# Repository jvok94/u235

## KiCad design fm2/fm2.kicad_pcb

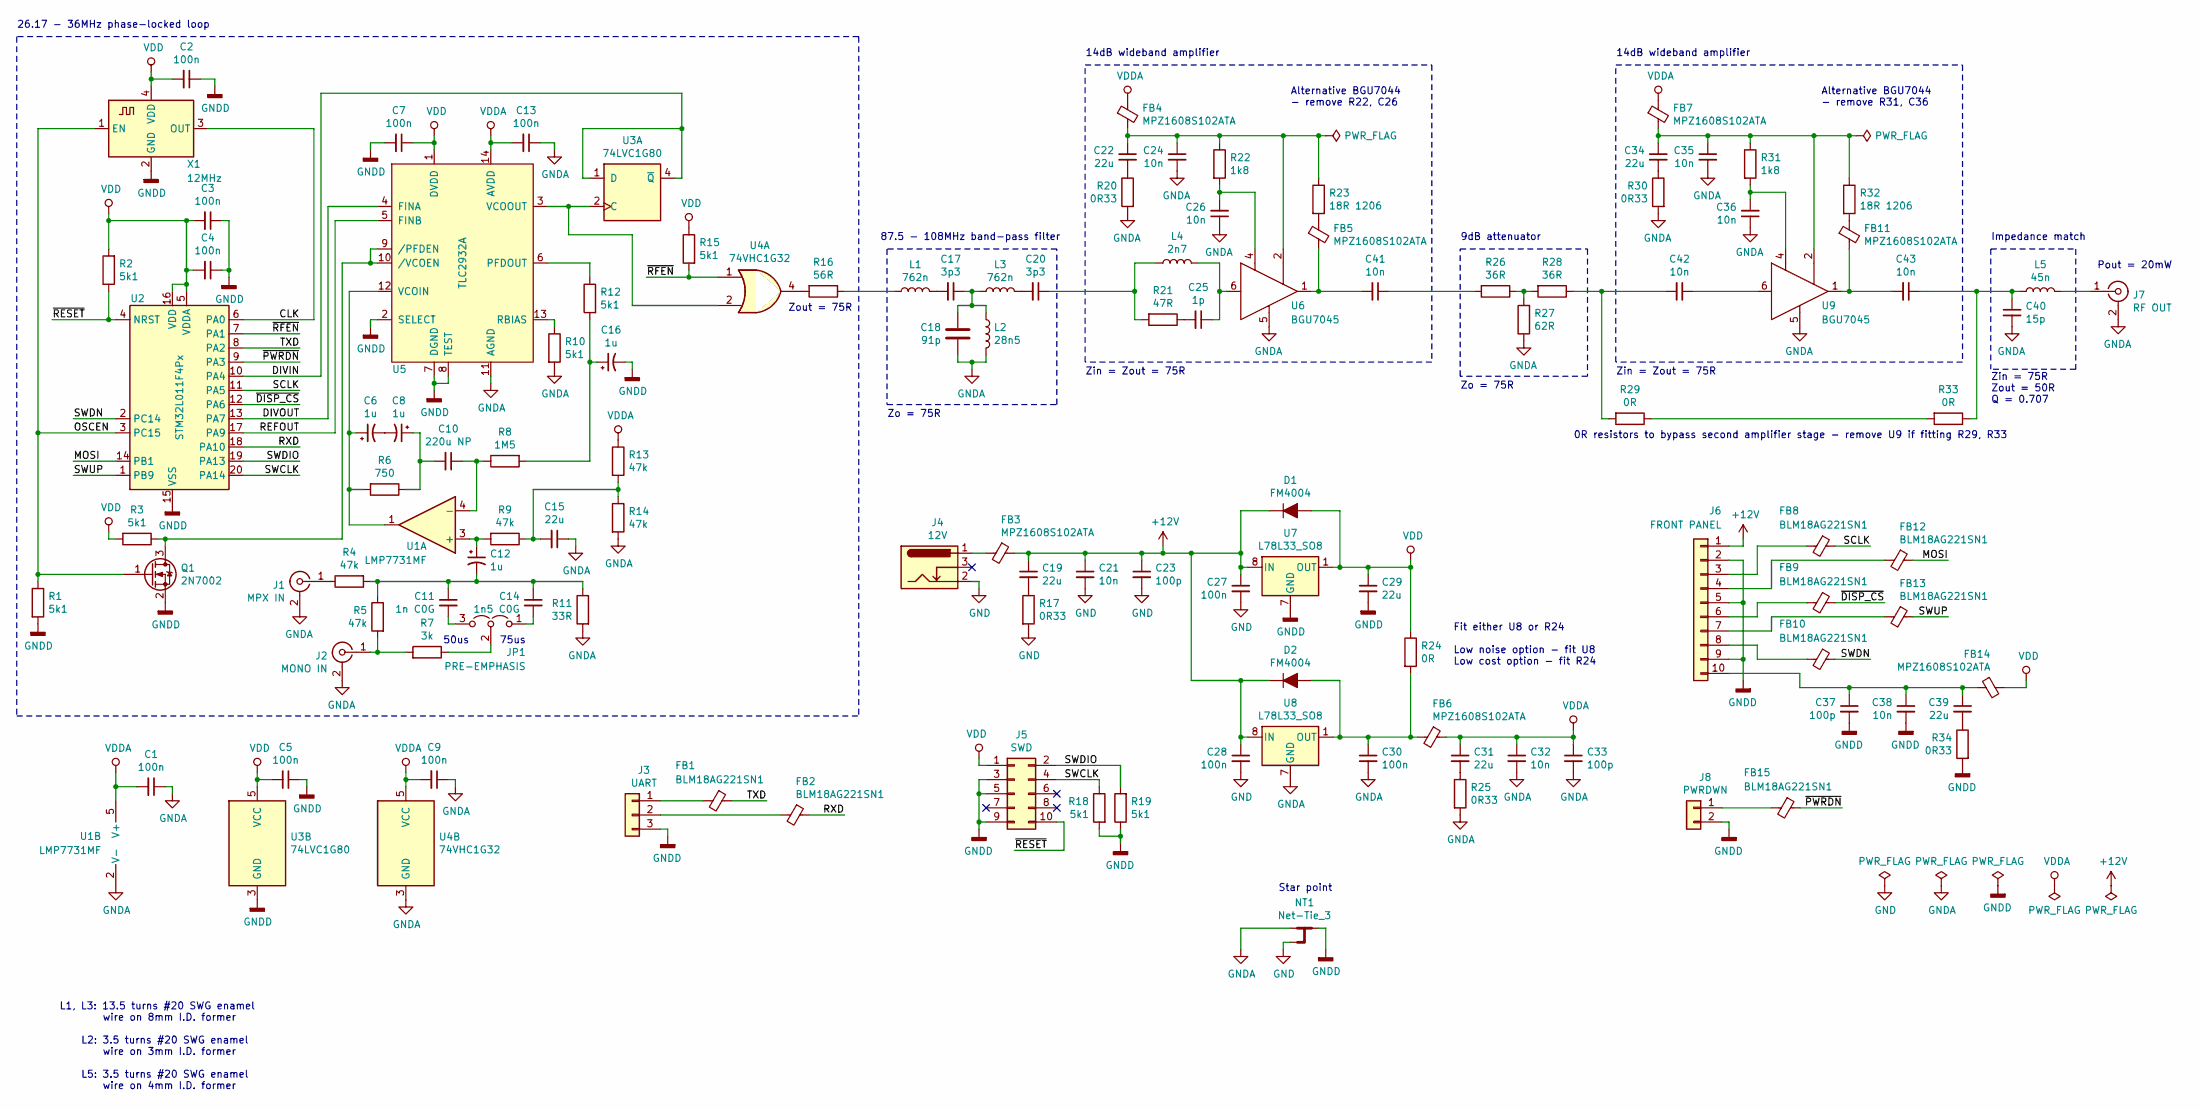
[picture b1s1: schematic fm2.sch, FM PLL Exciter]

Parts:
C1, C2, C3, C4, C5, C7, C9, C13, C27, C28, C30: 100n; C_0603_HandSoldering
C6, C8, C12, C16: 1u; CP_Radial_D5.0mm_P2.00mm
C10: 220u NP; CP_Radial_D8.0mm_P3.50mm
C11: 1n C0G; C_0603_HandSoldering
C14: 1n5 C0G; C_0603_HandSoldering
C15, C19, C22, C29, C31, C34, C39: 22u; C_1206_HandSoldering
C17, C20: 3p3; C_0603_HandSoldering
C18: 91p; C_0603_HandSoldering
C21, C24, C26, C32, C35, C36, C38, C41, C42, C43: 10n; C_0603_HandSoldering
C23, C33, C37: 100p; C_0603_HandSoldering
C25: 1p; C_0603_HandSoldering
C40: 15p; C_0603_HandSoldering
D1, D2: FM4004; D_SMA_Handsoldering
FB1, FB2, FB8, FB9, FB10, FB12, FB13, FB15: BLM18AG221SN1; R_0603_HandSoldering
FB3, FB4, FB5, FB6, FB7, FB11, FB14: MPZ1608S102ATA; R_0603_HandSoldering
J1: MPX IN; NYS354
J2: MONO IN; NYS354
J3: UART; Pin_Header_Straight_1x03_Pitch2.54mm
J4: 12V; BARREL_JACK
J5: SWD; Pin_Header_Straight_2x05_Pitch1.27mm
J6: FRONT PANEL; Pin_Header_Straight_1x10_Pitch2.54mm
J7: RF OUT; bnc-ci
J8: PWRDWN; Pin_Header_Straight_1x02_Pitch2.54mm
JP1: PRE-EMPHASIS; Pin_Header_Straight_1x03_Pitch2.54mm
L1, L3: 762n; Coil_D10mm_L14mm
L2: 28n5; Coil_D5mm_L4mm
L4: 2n7; R_0402_NoSilk
L5: 45n; Coil_D6mm_L4mm
NT1: Net-Tie_3; net_tie_3
Q1: 2N7002; SOT-23_Handsoldering
R1, R2, R3, R10, R12, R15, R18, R19: 5k1; R_0603_HandSoldering
R4, R5, R9, R13, R14: 47k; R_0603_HandSoldering
R6: 750; R_0603_HandSoldering
R7: 3k; R_0603_HandSoldering
R8: 1M5; R_0603_HandSoldering
R11: 33R; R_0603_HandSoldering
R16: 56R; R_0603_HandSoldering
R17, R20, R25, R30, R34: 0R33; R_0603_HandSoldering
R21: 47R; R_0603_HandSoldering
R22, R31: 1k8; R_0603_HandSoldering
R23, R32: 18R 1206; R_1206_HandSoldering
R24, R29, R33: 0R; R_0603_HandSoldering
R26, R28: 36R; R_0603_HandSoldering
R27: 62R; R_0603_HandSoldering
U1: LMP7731MF; SOT-23-5_HandSoldering
U2: STM32L011F4Px; TSSOP-20_4.4x6.5mm_P0.65mm
U3: 74LVC1G80; SOT-23-5_HandSoldering
U4: 74VHC1G32; SOT-753
U5: TLC2932A; TSSOP-14_4.4x5mm_P0.65mm
U6, U9: BGU7045; SOT-363_SC-70-6_Handsoldering
U7, U8: L78L33_SO8; SOIC-8_3.9x4.9mm_P1.27mm
X1: 12MHz; Crystal_SMD_5032-4pin_5.0x3.2mm

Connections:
+12V: C19.1, C21.1, C23.1, C27.1, C28.1, D1.1 (K), D2.1 (K), FB3.1, J6.1, U7.8 (IN), U8.8 (IN)
/CLK: U2.6 (PA0), X1.3 (OUT)
/DIVIN: U2.10 (PA4), U3.1 (D), U3.4 (~Q)
/DIVOUT: U2.13 (PA7), U5.4 (FINA)
/MOSI: FB12.1, U2.14 (PB1)
/OSCEN: Q1.1 (G), R1.1, U2.3 (PC15), X1.1 (EN)
/REFOUT: U2.17 (PA9), U5.5 (FINB)
/RXD: FB2.1, U2.18 (PA10)
/SCLK: FB8.1, U2.11 (PA5)
/SWCLK: J5.4, R18.1, U2.20 (PA14)
/SWDIO: J5.2, R19.2, U2.19 (PA13)
/SWDN: FB10.1, U2.2 (PC14)
/SWUP: FB13.1, U2.1 (PB9)
/TXD: FB1.1, U2.8 (PA2)
/~DISP_CS: FB9.1, U2.12 (PA6)
/~PWRDN: FB15.1, U2.9 (PA3)
/~RESET: J5.10, R2.1, U2.4 (NRST)
/~RFEN: R15.2, U2.7 (PA1), U4.1
GND: C21.2, C23.2, C27.2, C28.2, J4.2, NT1.3, R17.2
GNDA: C1.1, C9.1, C13.1, C15.1, C18.1, C24.2, C26.1, C30.2, C32.2, C33.2, C35.2, C36.1, C40.2, J1.2 (Ext), J2.2 (Ext), J7.2 (Ext), L2.2, NT1.1, R10.2, R11.2, R14.2, R20.2, R25.2, R27.1, R30.2, U1.2 (V-), U4.3 (GND), U5.11 (AGND), U6.5 (GND), U8.2 (GND), U8.3 (GND), U8.6 (GND), U8.7 (GND), U9.5 (GND)
GNDD: C2.1, C3.1, C4.1, C5.1, C7.2, C16.2, C29.2, C37.2, C38.2, J3.3, J5.3, J5.5, J5.9, J6.2, J6.5, J6.9, J8.2, NT1.2, Q1.2 (S), R1.2, R18.2, R19.1, R34.2, U2.15 (VSS), U3.3 (GND), U5.2 (SELECT), U5.7 (DGND), U5.8 (TEST), U7.2 (GND), U7.3 (GND), U7.6 (GND), U7.7 (GND), X1.2 (GND)
unnamed: C6.1, R6.2, U1.1, U5.12 (VCOIN)
unnamed: C6.2, C8.2
unnamed: C10.1, R8.1, U1.4 (-)
unnamed: C8.1, C10.2, R6.1
unnamed: C11.1, C12.2, C14.1, R4.2, R5.1, R11.1
unnamed: C11.2, JP1.3 (B)
unnamed: C12.1, R9.2, U1.3 (+)
unnamed: C14.2, JP1.1 (A)
unnamed: C15.2, R9.1, R13.2, R14.1
unnamed: C16.1, R8.2, R12.2
unnamed: C17.1, C18.2, L2.1, L3.1
unnamed: C17.2, L1.2
unnamed: C19.2, R17.1
unnamed: C20.1, L4.1, R21.2
unnamed: C20.2, L3.2
unnamed: C22.1, C24.1, FB4.2, R22.1, R23.1, U6.2 (VCC)
unnamed: C22.2, R20.1
unnamed: C25.1, L4.2, U6.6 (IN)
unnamed: C25.2, R21.1
unnamed: C26.2, R22.2, U6.4 (CTRL)
unnamed: C30.1, D2.2 (A), FB6.2, R24.2, U8.1 (OUT)
unnamed: C31.2, R25.1
unnamed: C34.1, C35.1, FB7.2, R31.1, R32.1, U9.2 (VCC)
unnamed: C34.2, R30.1
unnamed: C36.2, R31.2, U9.4 (CTRL)
unnamed: C37.1, C38.1, C39.1, FB14.1, J6.10
unnamed: C39.2, R34.1
unnamed: C40.1, C43.1, L5.1, R33.1
unnamed: C41.1, R26.2
unnamed: C41.2, FB5.2, U6.1 (OUT)
unnamed: C42.1, U9.6 (IN)
unnamed: C42.2, R28.1, R29.2
unnamed: C43.2, FB11.2, U9.1 (OUT)
unnamed: FB1.2, J3.1
unnamed: FB2.2, J3.2
unnamed: FB3.2, J4.1
unnamed: FB5.1, R23.2
unnamed: FB8.2, J6.3
unnamed: FB9.2, J6.6
unnamed: FB10.2, J6.8
unnamed: FB11.1, R32.2
unnamed: FB12.2, J6.4
unnamed: FB13.2, J6.7
unnamed: FB15.2, J8.1
unnamed: J1.1 (In), R4.1
unnamed: J2.1 (In), R5.2, R7.2
unnamed: J7.1 (In), L5.2
unnamed: JP1.2 (C), R7.1
unnamed: L1.1, R16.1
unnamed: Q1.3 (D), R3.1, U5.9 (/PFDEN), U5.10 (/VCOEN)
unnamed: R10.1, U5.13 (RBIAS)
unnamed: R12.1, U5.6 (PFDOUT)
unnamed: R16.2, U4.4
unnamed: R26.1, R27.2, R28.2
unnamed: R29.1, R33.2
unnamed: U3.2 (C), U4.2, U5.3 (VCOOUT)
VDD: C2.2, C3.2, C4.2, C5.2, C7.1, C29.1, D1.2 (A), FB14.2, J5.1, R2.2, R3.2, R15.1, R24.1, U2.5 (VDDA), U2.16 (VDD), U3.5 (VCC), U5.1 (DVDD), U7.1 (OUT), X1.4 (VDD)
VDDA: C1.2, C9.2, C13.2, C31.1, C32.1, C33.1, FB4.1, FB6.1, FB7.1, R13.1, U1.5 (V+), U4.5 (VCC), U5.14 (AVDD)

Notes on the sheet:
75us
50us
26.17 - 36MHz phase-locked loop
Zout = 75R
14dB wideband amplifier
Zin = Zout = 75R
Alternative BGU7044 - remove R22, C26
9dB attenuator
Alternative BGU7044 - remove R31, C36
0R resistors to bypass second amplifier stage - remove U9 if fitting R29, R33
Fit either U8 or R24 Low noise option - fit U8 Low cost option - fit R24
Star point
Pout = 20mW
Impedance match
Zin = 75R Zout = 50R Q = 0.707
L1, L3: 13.5 turns #20 SWG enamel wire on 8mm I.D. former L2: 3.5 turns #20 SWG enamel wire on 3mm I.D. former L5: 3.5 turns #20 SWG enamel wire on 4mm I.D. former
Zo = 75R
87.5 - 108MHz band-pass filter

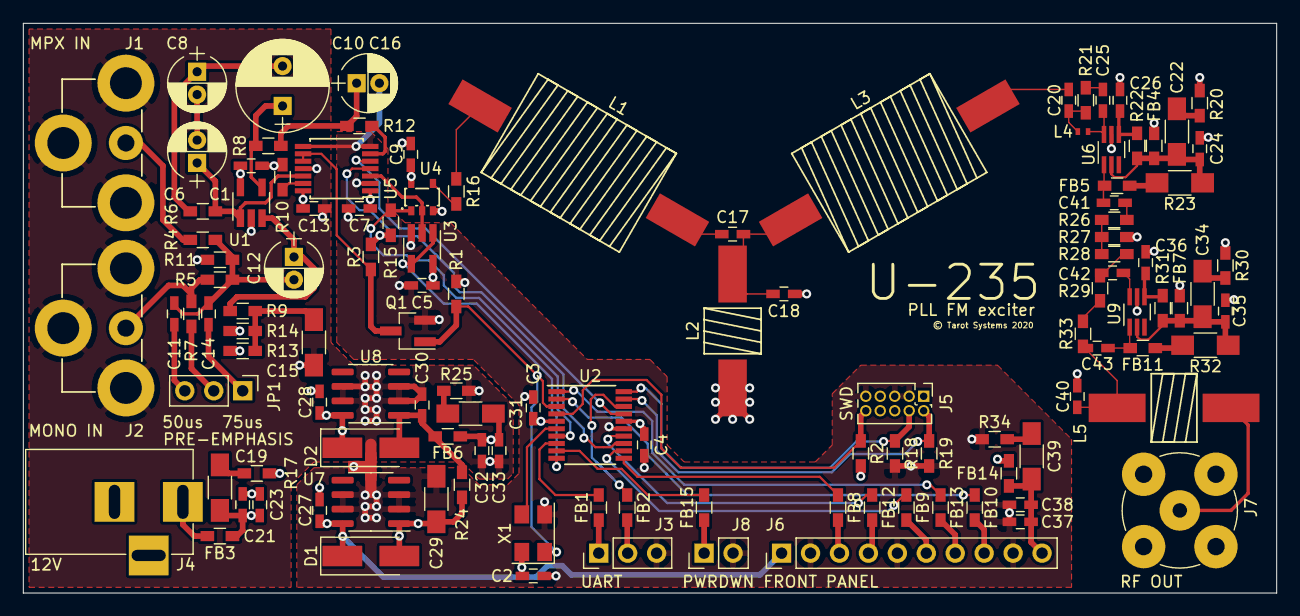
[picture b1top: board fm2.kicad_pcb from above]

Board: 4 copper layers, 110.0 x 50.0 mm, 120 parts (0 on the bottom side), 79 nets.

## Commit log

2020-06-21 Mark 1

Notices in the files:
fm2/fm2.kicad_pcb:
© Tarot Systems 2020
